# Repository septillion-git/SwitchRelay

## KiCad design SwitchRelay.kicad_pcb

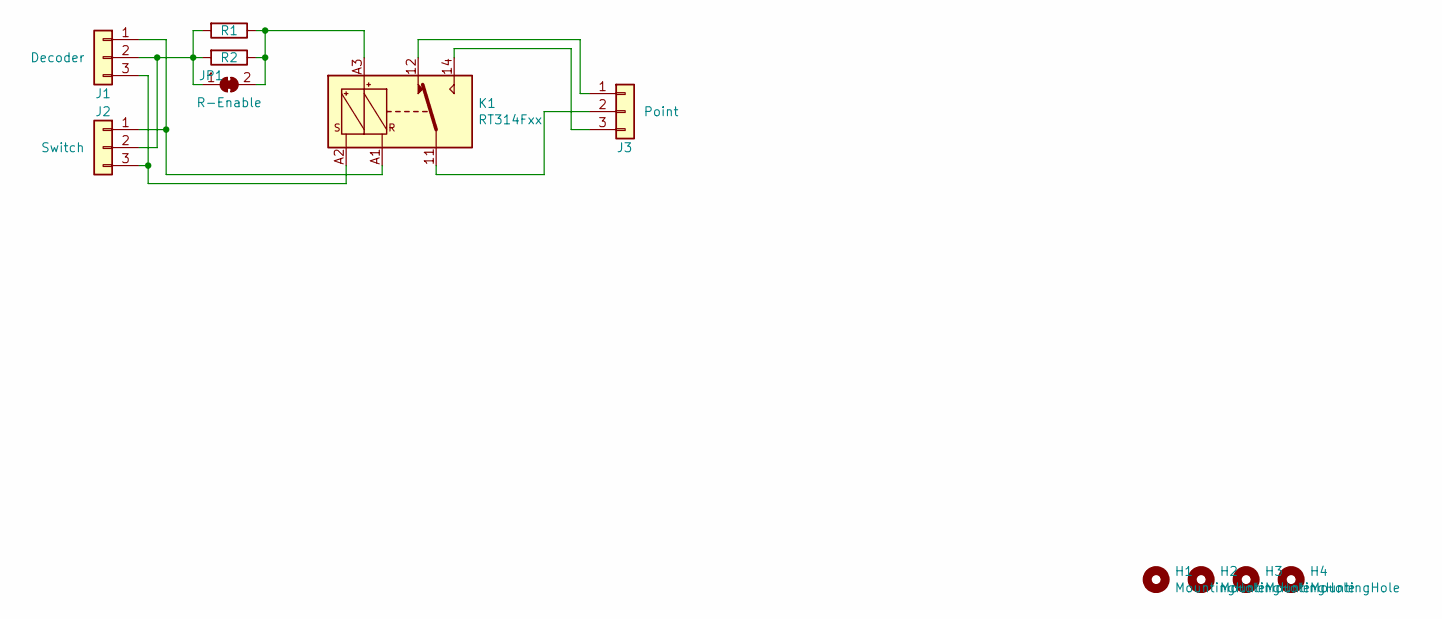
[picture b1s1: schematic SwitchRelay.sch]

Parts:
H1, H2, H3, H4: MountingHole; MountingHole_3mm
J1: Decoder; TerminalBlock_bornier-3_P5.08mm
J2: Switch; TerminalBlock_bornier-3_P5.08mm
J3: Point; TerminalBlock_bornier-3_P5.08mm
JP1: R-Enable; SolderJumper-2_P1.3mm_Bridged_RoundedPad1.0x1.5mm
K1: RT314Fxx; RTxxxFxx
R1: R; R_Axial_DIN0207_L6.3mm_D2.5mm_P7.62mm_Horizontal
R2: R; R_0805_2012Metric

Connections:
unnamed: J1.1, J2.1, K1.A1
unnamed: J1.2, J2.2, JP1.1 (A), R1.2, R2.2
unnamed: J1.3, J2.3, K1.A2
unnamed: J3.1, K1.12
unnamed: J3.2, K1.11
unnamed: J3.3, K1.14
unnamed: JP1.2 (B), K1.A3, R1.1, R2.1

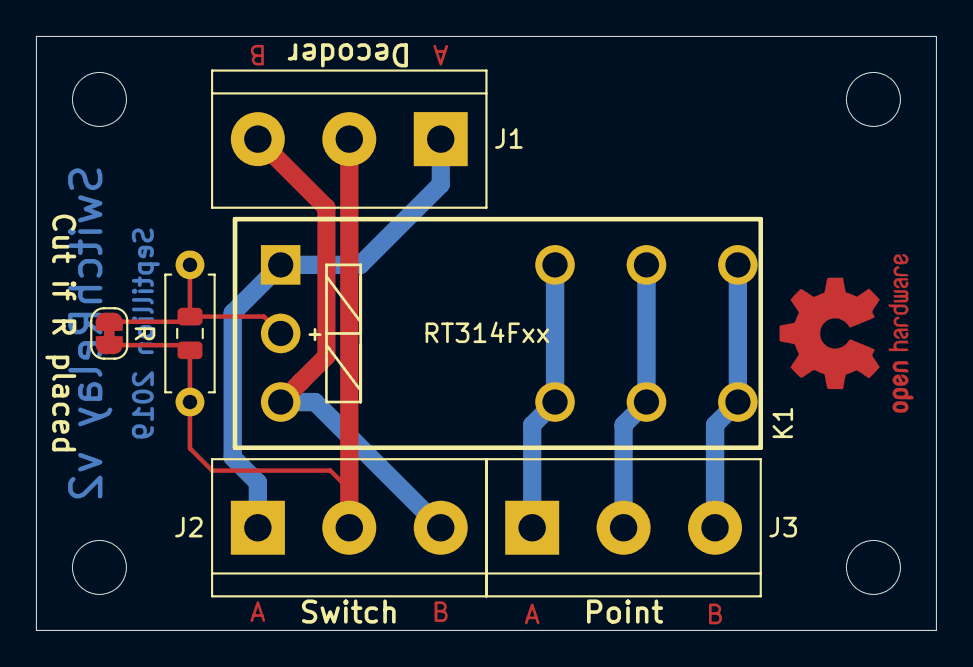
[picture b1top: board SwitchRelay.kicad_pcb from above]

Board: 2 copper layers, 50.0 x 33.0 mm, 11 parts (0 on the bottom side), 7 nets.

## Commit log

2019-09-02 :octocat: Added .gitattributes & .gitignore files
2019-09-02 First versioning
2019-09-02 Made version 2 with RT314F24
2019-09-09 Small changes
2019-09-09 added single panel gerbers
2019-09-09 Added 2x3 (100x99mm) panel
